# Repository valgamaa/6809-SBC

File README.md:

# 6809 SBC

A self-built 6809 single-board computer that runs **FLEX 9** from a
CompactFlash card: schematics and boards, the firmware and drivers that run
on it, and the host-side tools used with it.

## Contents

| Folder | Contents |
|---|---|
| [`hardware/`](hardware/) | Schematics and board files (current version: V6) |
| [`software/`](software/) | Monitor, FLEX BIOS and disk drivers, RTC support, CF tools and the ROM image — see [software/README.md](software/README.md) |
| [`tools/octave/`](tools/octave/) | Octave scripts for FLEX disk images and S-record handling |

The companion Mac application [A09Studio](https://github.com/valgamaa/A09Studio)
assembles the code, programs the ROM, sends FLEX disk images to the CF card,
and browses and builds FLEX disks.

## Licence

The code in this repository is released under the [MIT licence](LICENSE).
Parts derive from third-party software; see [NOTICE.md](NOTICE.md). FLEX and
TSC programs are not included and belong to their owners.

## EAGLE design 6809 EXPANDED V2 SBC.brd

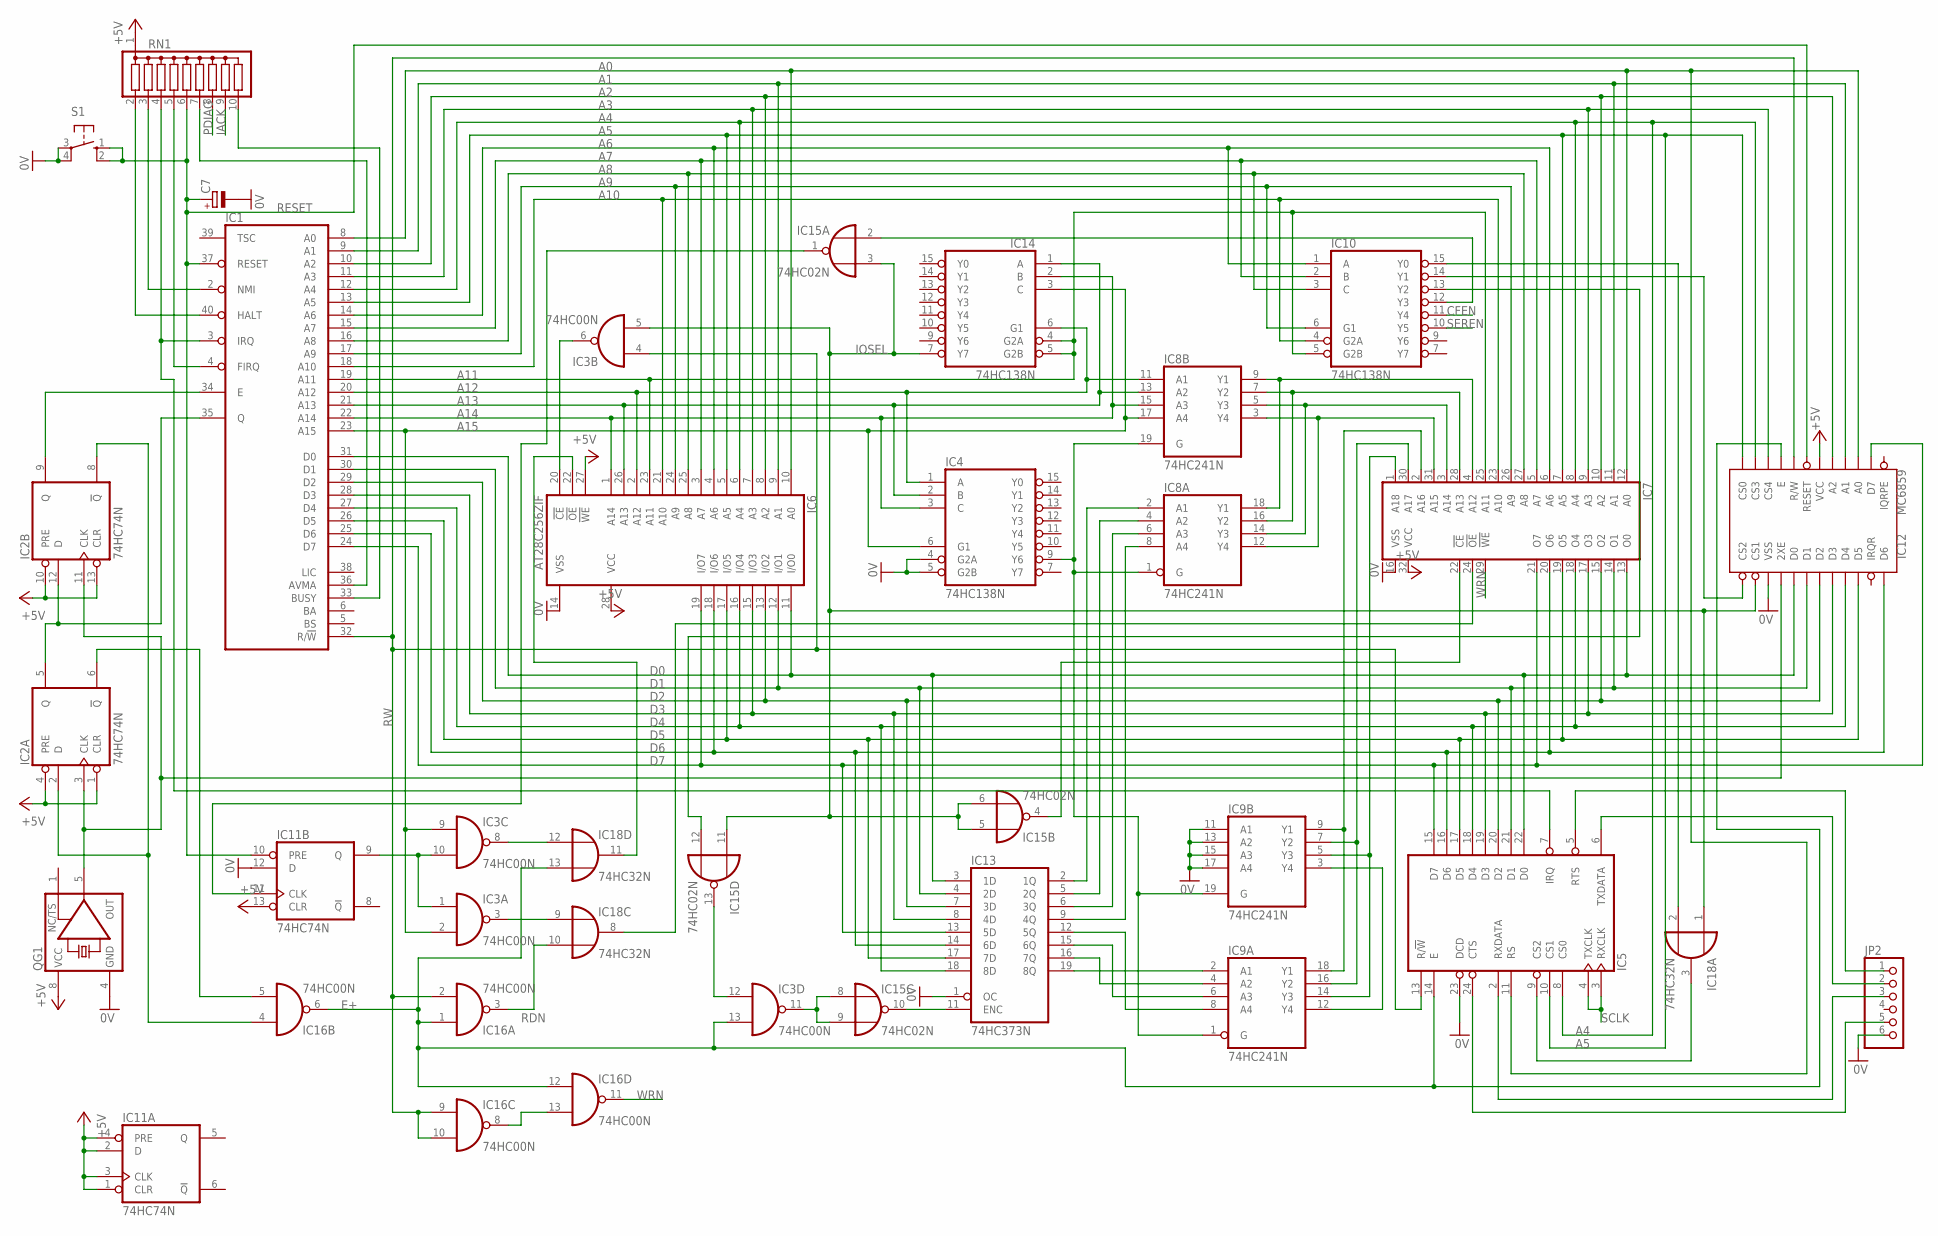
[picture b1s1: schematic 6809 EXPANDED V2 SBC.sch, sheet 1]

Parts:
C7: CPOL-EUE2-5; E2-5
IC1: 6809E; DIL40
IC2, IC11: 74HC74N; DIL14
IC3, IC16: 74HC00N; DIL14
IC4, IC10, IC14: 74HC138N; DIL16
IC5: 6850; DIL24
IC6: AT28C256ZIF; 228-1277-00-0602J
IC7: AS6C4008; DIL32
IC8, IC9: 74HC241N; DIL20
IC12: MC6859; DIL24-6
IC13: 74HC373N; DIL20
IC15: 74HC02N; DIL14
IC18: 74HC32N; DIL14
JP2: PINHD-1X6/90; 1X06/90
QG1: XO-8; DIL08S
RN1: G09R; SIL10
S1: 10-XX; B3F-10XX

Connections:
0V: C7.-, IC4.4 (G2A), IC4.5 (G2B), IC5.23 (DCD), IC6.14 (VSS), IC7.16 (VSS), IC9.11 (A1), IC9.13 (A2), IC9.15 (A3), IC9.17 (A4), IC11.12 (D), IC12.15 (VSS), IC13.1 (OC), JP2.6, QG1.4 (GND), S1.3, S1.4 (P1); also elsewhere on the board
+5V: IC2.1 (CLR), IC2.4 (PRE), IC2.10 (PRE), IC2.13 (CLR), IC6.27 (!WE), IC6.28 (VCC), IC7.32 (VCC), IC11.1 (CLR), IC11.2 (D), IC11.3 (CLK), IC11.4 (PRE), IC11.13 (CLR), IC12.6 (VCC), QG1.8 (VCC), RN1.1; also elsewhere on the board
A0: IC1.8 (A0), IC5.11 (RS), IC6.10 (A0), IC7.12 (A0), IC12.3 (A0); also elsewhere on the board
A1: IC1.9 (A1), IC6.9 (A1), IC7.11 (A1), IC12.4 (A1); also elsewhere on the board
A2: IC1.10 (A2), IC6.8 (A2), IC7.10 (A2), IC12.5 (A2); also elsewhere on the board
A3: IC1.11 (A3), IC6.7 (A3), IC7.9 (A3), IC12.10 (CS4); also elsewhere on the board
A4: IC1.12 (A4), IC5.8 (CS0), IC6.6 (A4), IC7.8 (A4), IC12.11 (CS3); also elsewhere on the board
A5: IC1.13 (A5), IC5.10 (CS1), IC6.5 (A5), IC7.7 (A5), IC12.12 (CS0); also elsewhere on the board
A6: IC1.14 (A6), IC6.4 (A6), IC7.6 (A6), IC10.1 (A)
A7: IC1.15 (A7), IC6.3 (A7), IC7.5 (A7), IC10.2 (B)
A8: IC1.16 (A8), IC6.25 (A8), IC7.27 (A8), IC10.3 (C)
A9: IC1.17 (A9), IC6.24 (A9), IC7.26 (A9), IC10.6 (G1)
A10: IC1.18 (A10), IC6.21 (A10), IC7.23 (A10), IC10.4 (G2A)
A11: IC1.19 (A11), IC6.23 (A11), IC7.25 (A11), IC10.5 (G2B), IC14.4 (G2A), IC14.5 (G2B)
A12: IC1.20 (A12), IC4.1 (A), IC6.2 (A12), IC8.11 (A1), IC14.6 (G1)
A13: IC1.21 (A13), IC4.2 (B), IC6.26 (A13), IC8.13 (A2), IC14.1 (A)
A14: IC1.22 (A14), IC4.3 (C), IC6.1 (A14), IC8.15 (A3), IC14.2 (B)
A15: IC1.23 (A15), IC3.2 (I1), IC3.9 (I0), IC4.6 (G1), IC8.17 (A4), IC14.3 (C)
CFEN: IC10.11 (Y4); also elsewhere on the board
D0: IC1.31 (D0), IC5.22 (D0), IC6.11 (I/O0), IC7.13 (O0), IC12.17 (D0), IC13.3 (1D); also elsewhere on the board
D1: IC1.30 (D1), IC5.21 (D1), IC6.12 (I/O1), IC7.14 (O1), IC12.18 (D1), IC13.4 (2D); also elsewhere on the board
D2: IC1.29 (D2), IC5.20 (D2), IC6.13 (I/O2), IC7.15 (O2), IC12.19 (D2), IC13.7 (3D); also elsewhere on the board
D3: IC1.28 (D3), IC5.19 (D3), IC6.15 (I/O3), IC7.17 (O3), IC12.20 (D3), IC13.8 (4D); also elsewhere on the board
D4: IC1.27 (D4), IC5.18 (D4), IC6.16 (I/O4), IC7.18 (O4), IC12.21 (D4), IC13.18 (8D); also elsewhere on the board
D5: IC1.26 (D5), IC5.17 (D5), IC6.17 (I/O5), IC7.19 (O5), IC12.22 (D5), IC13.17 (7D); also elsewhere on the board
D6: IC1.25 (D6), IC5.16 (D6), IC6.18 (I/O6), IC7.20 (O6), IC12.24 (D6), IC13.14 (6D); also elsewhere on the board
D7: IC1.24 (D7), IC5.15 (D7), IC6.19 (I/O7), IC7.21 (O7), IC12.2 (D7), IC13.13 (5D); also elsewhere on the board
E+: IC3.13 (I1), IC5.14 (E), IC12.9 (E), IC16.1 (I0), IC16.6 (O), IC16.12 (I0), IC18.13 (I1)
IACK: RN1.9; also elsewhere on the board
IOSEL: IC3.5 (I1), IC12.14 (CS1), IC14.7 (Y7), IC15.3 (I1), IC15.5 (I0), IC15.6 (I1), IC15.11 (I0), IC18.1 (I0); also elsewhere on the board
unnamed: IC2.6 (!Q), IC16.5 (I1)
unnamed: IC2.2 (D), IC2.8 (!Q), IC16.4 (I0)
unnamed: IC2.3 (CLK), IC2.11 (CLK), IC12.16 (2XE), QG1.5 (OUT)
unnamed: IC1.4 (FIRQ), RN1.5
unnamed: IC1.35 (Q), IC2.5 (Q), IC2.12 (D)
unnamed: IC3.12 (I0), IC15.13 (O)
unnamed: IC10.13 (Y2), IC15.12 (I1)
unnamed: IC3.11 (O), IC15.8 (I0), IC15.9 (I1)
unnamed: IC1.34 (E), IC2.9 (Q)
unnamed: IC3.1 (I0), IC3.10 (I1), IC11.9 (Q)
unnamed: IC7.22 (!CE), IC15.4 (O)
unnamed: IC10.12 (Y3), IC15.2 (I0)
unnamed: IC3.3 (O), IC18.9 (I0)
unnamed: IC11.11 (CLK), IC15.1 (O)
unnamed: IC7.24 (!OE), IC18.8 (O)
unnamed: IC6.22 (!OE), IC18.11 (O)
unnamed: IC9.2 (A1), IC13.19 (8Q)
unnamed: IC13.11 (ENC), IC15.10 (O)
unnamed: IC16.8 (O), IC16.13 (I1)
unnamed: IC3.8 (O), IC18.12 (I0)
unnamed: IC10.14 (Y1), IC12.13 (CS2)
unnamed: IC5.5 (RTS), JP2.1
unnamed: IC1.40 (HALT), RN1.2
unnamed: IC3.6 (O), IC6.20 (!CE)
unnamed: IC1.36 (AVMA), RN1.7
unnamed: IC1.33 (BUSY), RN1.10
unnamed: IC1.3 (IRQ), IC5.7 (IRQ), RN1.4
unnamed: IC5.24 (CTS), JP2.5
unnamed: IC1.2 (NMI), RN1.3
unnamed: IC5.6 (TXDATA), JP2.2
unnamed: IC5.2 (RXDATA), JP2.3
unnamed: IC4.9 (Y6), IC8.1 (G), IC8.19 (G), IC9.1 (G), IC9.19 (G)
unnamed: IC7.4 (A12), IC8.9 (Y1), IC8.18 (Y1)
unnamed: IC7.28 (A13), IC8.7 (Y2), IC8.16 (Y2)
unnamed: IC7.3 (A14), IC8.5 (Y3), IC8.14 (Y3)
unnamed: IC7.31 (A15), IC8.3 (Y4), IC8.12 (Y4)
unnamed: IC9.8 (A4), IC13.12 (5Q)
unnamed: IC10.15 (Y0), IC18.2 (I1)
unnamed: IC9.4 (A2), IC13.16 (7Q)
unnamed: IC9.6 (A3), IC13.15 (6Q)
unnamed: IC7.2 (A16), IC9.9 (Y1), IC9.18 (Y1)
unnamed: IC7.30 (A17), IC9.7 (Y2), IC9.16 (Y2)
unnamed: IC7.1 (A18), IC9.5 (Y3), IC9.14 (Y3)
unnamed: IC9.3 (Y4), IC9.12 (Y4)
unnamed: IC8.8 (A4), IC13.9 (4Q)
unnamed: IC8.6 (A3), IC13.6 (3Q)
unnamed: IC8.4 (A2), IC13.5 (2Q)
unnamed: IC8.2 (A1), IC13.2 (1Q)
unnamed: IC5.9 (CS2), IC18.3 (O)
PDIAG: RN1.8; also elsewhere on the board
RDN: IC16.3 (O), IC18.10 (I1); also elsewhere on the board
RESET: C7.+, IC1.37 (RESET), IC11.10 (PRE), IC12.7 (RESET), RN1.6, S1.1 (S), S1.2 (S1); also elsewhere on the board
RW: IC1.32 (R/!W), IC3.4 (I0), IC5.13 (R/!W), IC12.8 (R/W), IC16.2 (I1), IC16.9 (I0), IC16.10 (I1); also elsewhere on the board
SCLK: IC5.3 (RXCLK), IC5.4 (TXCLK); also elsewhere on the board
SEREN: IC10.10 (Y5); also elsewhere on the board
WRN: IC7.29 (!WE), IC16.11 (O); also elsewhere on the board

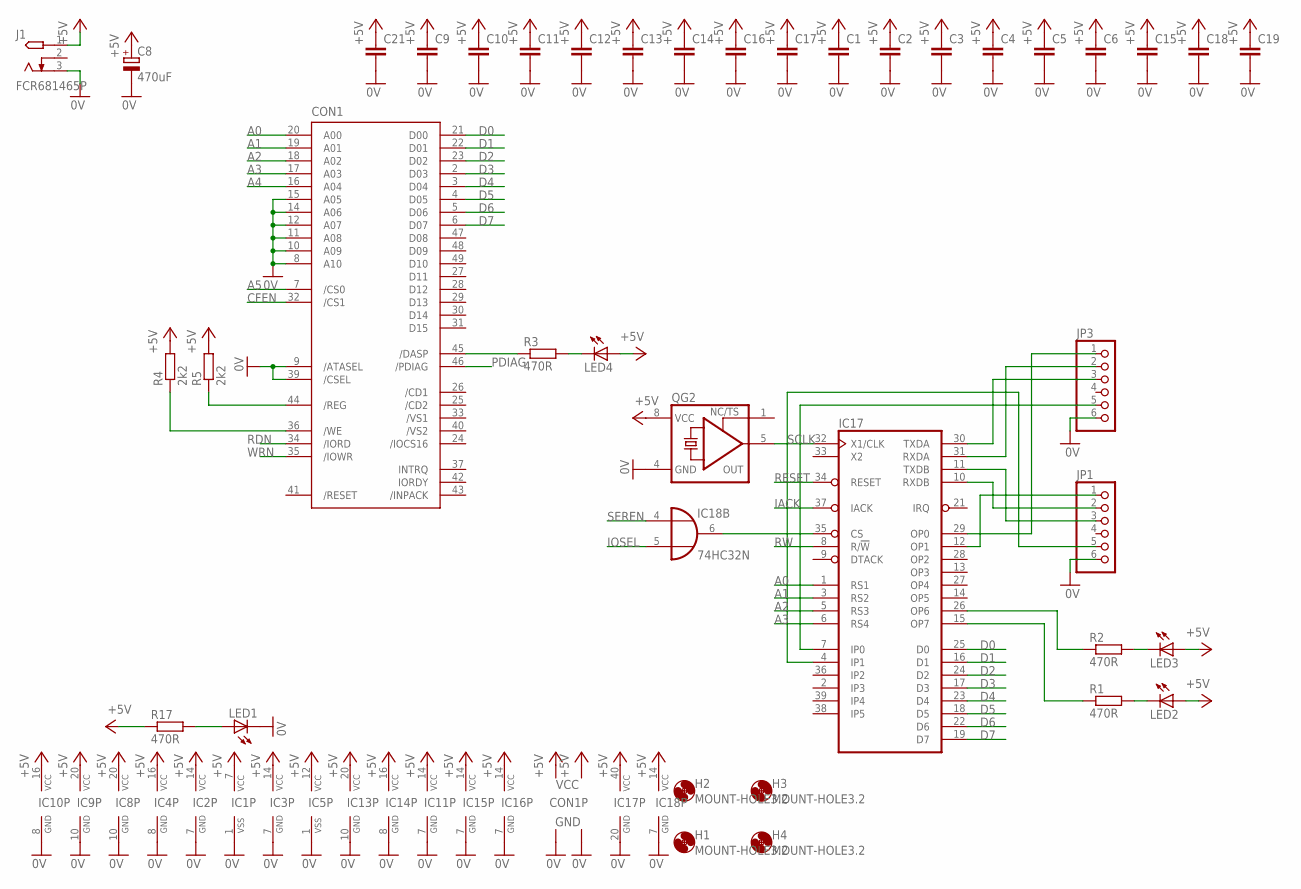
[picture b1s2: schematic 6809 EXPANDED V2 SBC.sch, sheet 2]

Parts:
C1, C2, C3, C4, C5, C6, C9, C10, C11, C12, C13, C14, C15, C16, C17, C18, C19, C21: C-EU025-025X050; C025-025X050
C8: 470uF; E5-10,5
CON1: CF-CARD-IDE_MODE; MI20-50PD-SF
H1, H2, H3, H4: MOUNT-HOLE3.2; 3,2
IC1: 6809E; DIL40
IC2, IC11: 74HC74N; DIL14
IC3, IC16: 74HC00N; DIL14
IC4, IC10, IC14: 74HC138N; DIL16
IC5: 6850; DIL24
IC8, IC9: 74HC241N; DIL20
IC13: 74HC373N; DIL20
IC15: 74HC02N; DIL14
IC17: MC68681P; DIL40
IC18: 74HC32N; DIL14
J1: FCR681465P
JP1, JP3: PINHD-1X6/90; 1X06/90
LED1, LED2, LED3, LED4: LED3MM
QG2: XO-8; DIL08S
R1, R2, R3, R17: 470R; 0207/10
R4, R5: 2k2; 0207/10

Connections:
0V: C1.2, C2.2, C3.2, C4.2, C5.2, C6.2, C8.-, C9.2, C10.2, C11.2, C12.2, C13.2, C14.2, C15.2, C16.2, C17.2, C18.2, C19.2, C21.2, CON1.1 (GND1), CON1.8 (A10), CON1.9 (/ATASEL), CON1.10 (A09), CON1.11 (A08), CON1.12 (A07), CON1.14 (A06), CON1.15 (A05), CON1.39 (/CSEL), CON1.50 (GND2), IC1.1 (VSS), IC2.7 (GND), IC3.7 (GND), IC4.8 (GND), IC5.1 (VSS), IC8.10 (GND), IC9.10 (GND), IC10.8 (GND), IC11.7 (GND), IC13.10 (GND), IC14.8 (GND), IC15.7 (GND), IC16.7 (GND), IC17.20 (GND), IC18.7 (GND), J1.3, JP1.6, JP3.6, LED1.K (C), QG2.4 (GND); also elsewhere on the board
+5V: C1.1, C2.1, C3.1, C4.1, C5.1, C6.1, C8.+, C9.1, C10.1, C11.1, C12.1, C13.1, C14.1, C15.1, C16.1, C17.1, C18.1, C19.1, C21.1, CON1.13 (VCC2), CON1.38 (VCC1), IC1.7 (VCC), IC2.14 (VCC), IC3.14 (VCC), IC4.16 (VCC), IC5.12 (VCC), IC8.20 (VCC), IC9.20 (VCC), IC10.16 (VCC), IC11.14 (VCC), IC13.20 (VCC), IC14.16 (VCC), IC15.14 (VCC), IC16.14 (VCC), IC17.40 (VCC), IC18.14 (VCC), J1.1, LED2.A, LED3.A, LED4.A, QG2.8 (VCC), R4.2, R5.2, R17.1; also elsewhere on the board
A0: CON1.20 (A00), IC17.1 (RS1); also elsewhere on the board
A1: CON1.19 (A01), IC17.3 (RS2); also elsewhere on the board
A2: CON1.18 (A02), IC17.5 (RS3); also elsewhere on the board
A3: CON1.17 (A03), IC17.6 (RS4); also elsewhere on the board
A4: CON1.16 (A04); also elsewhere on the board
A5: CON1.7 (/CS0); also elsewhere on the board
CFEN: CON1.32 (/CS1); also elsewhere on the board
D0: CON1.21 (D00), IC17.25 (D0); also elsewhere on the board
D1: CON1.22 (D01), IC17.16 (D1); also elsewhere on the board
D2: CON1.23 (D02), IC17.24 (D2); also elsewhere on the board
D3: CON1.2 (D03), IC17.17 (D3); also elsewhere on the board
D4: CON1.3 (D04), IC17.23 (D4); also elsewhere on the board
D5: CON1.4 (D05), IC17.18 (D5); also elsewhere on the board
D6: CON1.5 (D06), IC17.22 (D6); also elsewhere on the board
D7: CON1.6 (D07), IC17.19 (D7); also elsewhere on the board
IACK: IC17.37 (IACK); also elsewhere on the board
IOSEL: IC18.5 (I1); also elsewhere on the board
unnamed: IC17.35 (CS), IC18.6 (O)
unnamed: LED1.A, R17.2
unnamed: IC17.31 (RXDA), JP3.2
unnamed: IC17.30 (TXDA), JP3.3
unnamed: IC17.11 (TXDB), JP1.3
unnamed: IC17.10 (RXDB), JP1.2
unnamed: IC17.7 (IP0), JP3.5
unnamed: IC17.4 (IP1), JP1.5
unnamed: IC17.29 (OP0), JP3.1
unnamed: LED3.K (C), R2.2
unnamed: IC17.12 (OP1), JP1.1
unnamed: LED2.K (C), R1.2
unnamed: IC17.26 (OP6), R2.1
unnamed: IC17.15 (OP7), R1.1
unnamed: CON1.45 (/DASP), R3.1
unnamed: LED4.K (C), R3.2
unnamed: CON1.44 (/REG), R5.1
unnamed: CON1.36 (/WE), R4.1
PDIAG: CON1.46 (/PDIAG); also elsewhere on the board
RDN: CON1.34 (/IORD); also elsewhere on the board
RESET: IC17.34 (RESET); also elsewhere on the board
RW: IC17.8 (R/!W); also elsewhere on the board
SCLK: IC17.32 (X1/CLK), QG2.5 (OUT); also elsewhere on the board
SEREN: IC18.4 (I0); also elsewhere on the board
WRN: CON1.35 (/IOWR); also elsewhere on the board

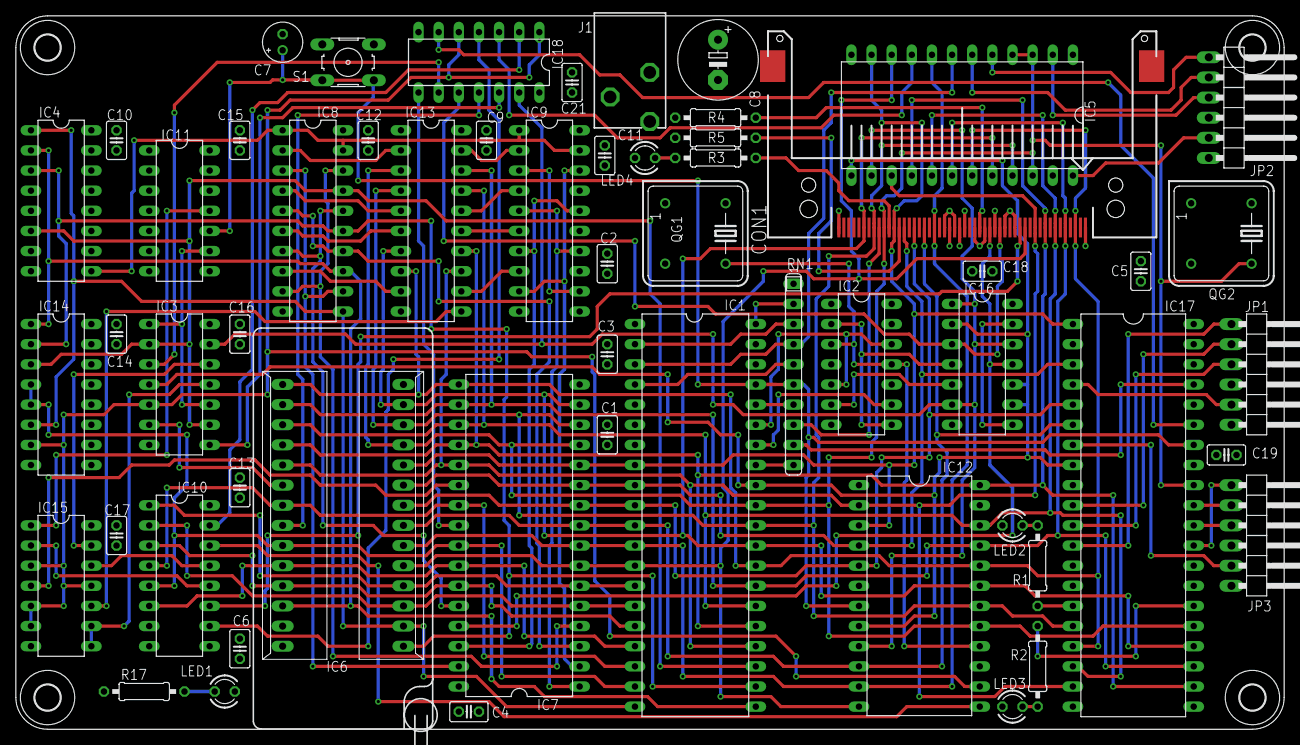
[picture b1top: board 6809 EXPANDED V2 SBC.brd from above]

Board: 4 copper layers, 160.0 x 90.0 mm, 61 parts (0 on the bottom side), 104 nets.

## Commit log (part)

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2022-08-10 Version 6 schematic, BOM and component placement
2024-03-27 Add files via upload
    Octave program to extract and list the directory of a .DSK file.
    filepath needs to point to directory containing the .DSK image, and filename set to the specific image to be processed.
    The directory is listed in the Command Window.
2024-04-29 Add files via upload
    Extracts any CMD, SYS or COR file from a DSK image, and converts the binary file to an s-record file that can be downloaded or programmed into the EEPROM on the SBC.
2024-04-29 Add files via upload
    Reads an s09 file and builds a memory map from the data. The address references are them sorted into ascending order and a new s09 file written back to disk. Flex.cor contains patches that overwrite 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
2024-07-22 Add files via upload
    The image is a composite of Assist09, the console drivers for Flex and an image of Flex 9.1.
    SortedFlex.s09 is a file that can be downloaded individually that is FLEX.COR - it is a full flex image, without the drivers included.
    Flex_BIOS.s09 contains the vector table that connects FLEX.COR with the console drivers, but does not contain the disk drivers.
    CF_Test_04.s09 is a utility for configuring CF Cards and reading/writing from/to them. This is used to create a Flex disk image on a CF Card, as part of bringing Flex to life.
    merged.hex is the image that can be programmed to the EEPROM.
